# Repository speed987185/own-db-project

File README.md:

# Pi Cloud Server

A personal local cloud storage system built with Raspberry Pi.

---

## ⚠️ Prototype Notice

> **This repository contains a prototype implementation built for demonstration and submission purposes. The current version is developed and tested on a standard computer. Final deployment and hardware integration with Raspberry Pi will be performed after receiving approval from Blueprint Hack Club.**

---

## Project Overview

This project demonstrates a self-hosted cloud storage concept using:

- **Flask** backend with REST API
- **PostgreSQL** database for file metadata
- **Raspberry Pi** as target deployment platform

The goal is to create a personal alternative to commercial cloud storage services.

---

## Repository Contents

| Folder                                 | Description                         |
| -------------------------------------- | ----------------------------------- |
| `pi-cloud-server/`                     | Backend server (Flask + PostgreSQL) |
| `CAD/`                                 | 3D enclosure designs                |
| `PCB & SHEMANTIC FOR EXTERNALL BOARD/` | Custom PCB for Pi expansion         |

---

## Hardware Design

### PCB Design

Custom expansion board providing additional ports and cooling support.

### CAD Enclosure

3D-printable enclosure with:

- Front/back removable panels
- SSD mounting slot
- Port cutouts for Pi and expansion board

---

## Quick Start

```bash
cd pi-cloud-server
pip install -r requirements.txt
python app.py
```

See `pi-cloud-server/README.md` for detailed instructions.

---

## Future Plans (Post-Grant Approval)

- Raspberry Pi 4 deployment
- External SSD integration
- Full file upload/download
- Web dashboard
- User authentication

---

## Contact

Email: mjlabishek123@gmail.com

---

## License

MIT License

---

_Built for Blueprint Hack Club_

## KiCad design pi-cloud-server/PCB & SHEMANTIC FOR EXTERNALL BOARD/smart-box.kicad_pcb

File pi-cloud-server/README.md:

# Pi Cloud Server

A lightweight local cloud storage server designed for Raspberry Pi.

---

## ⚠️ Prototype Notice

> **This repository contains a prototype implementation built for demonstration and submission purposes. The current version is developed and tested on a standard computer. Final deployment and hardware integration with Raspberry Pi will be performed after receiving approval from Blueprint Hack Club.**

---

## What is this?

Pi Cloud Server is a self-hosted cloud storage solution that runs on a Raspberry Pi. It provides:

- **File metadata storage** using PostgreSQL database
- **REST API** for managing files
- **Local network access** to your personal cloud

Think of it as your own mini Dropbox, running on a $35 computer in your home.

---

## What this demonstrates

- Flask backend development
- SQLAlchemy ORM integration
- PostgreSQL database usage
- RESTful API design
- Modular Python project structure

---

## Project Structure

```
pi-cloud-server/
├── app.py           # Main Flask application
├── config.py        # Configuration settings
├── models.py        # Database models (SQLAlchemy)
├── routes.py        # API endpoints
├── requirements.txt # Python dependencies
├── schema.sql       # Database schema (optional)
├── TODO.md          # Future development plans
└── storage/         # File storage directory (future use)
```

---

## Quick Start

### 1. Install dependencies

```bash
pip install -r requirements.txt
```

### 2. Set up PostgreSQL database

```bash
# Create database
psql -U postgres -c "CREATE DATABASE picloud_db;"
psql -U postgres -c "CREATE USER picloud WITH PASSWORD 'password';"
psql -U postgres -c "GRANT ALL PRIVILEGES ON DATABASE picloud_db TO picloud;"
```

### 3. Run the server

```bash
python app.py
```

Server will start at `http://localhost:5000`

---

## API Endpoints

| Method | Endpoint | Description |
|--------|----------|-------------|
| GET | `/` | Server status |
| GET | `/files` | List all files |
| POST | `/files` | Create file metadata |
| GET | `/files/<id>` | Get single file |
| DELETE | `/files/<id>` | Delete file |
| GET | `/stats` | Storage statistics |

---

## Example Usage

### Check server status
```bash
curl http://localhost:5000/
```

### Create file metadata
```bash
curl -X POST http://localhost:5000/files \
  -H "Content-Type: application/json" \
  -d '{"filename": "document.pdf", "size": 1024, "file_type": "application/pdf"}'
```

### List all files
```bash
curl http://localhost:5000/files
```

### Delete a file
```bash
curl -X DELETE http://localhost:5000/files/1
```

---

## Database Configuration

Default connection string:
```
postgresql://picloud:password@localhost:5432/picloud_db
```

Override with environment variable:
```bash
export DATABASE_URL="postgresql://user:pass@host:port/dbname"
```

---

## Future Plans

After Blueprint Hack Club grant approval:

- Deploy on Raspberry Pi 4
- Integrate external SSD storage
- Add actual file upload/download
- Implement user authentication
- Create web dashboard

See `TODO.md` for full roadmap.

---

## Tech Stack

- **Backend:** Python, Flask
- **Database:** PostgreSQL, SQLAlchemy
- **Target Hardware:** Raspberry Pi 4

---

## License

MIT License

---

*Built for Blueprint Hack Club*

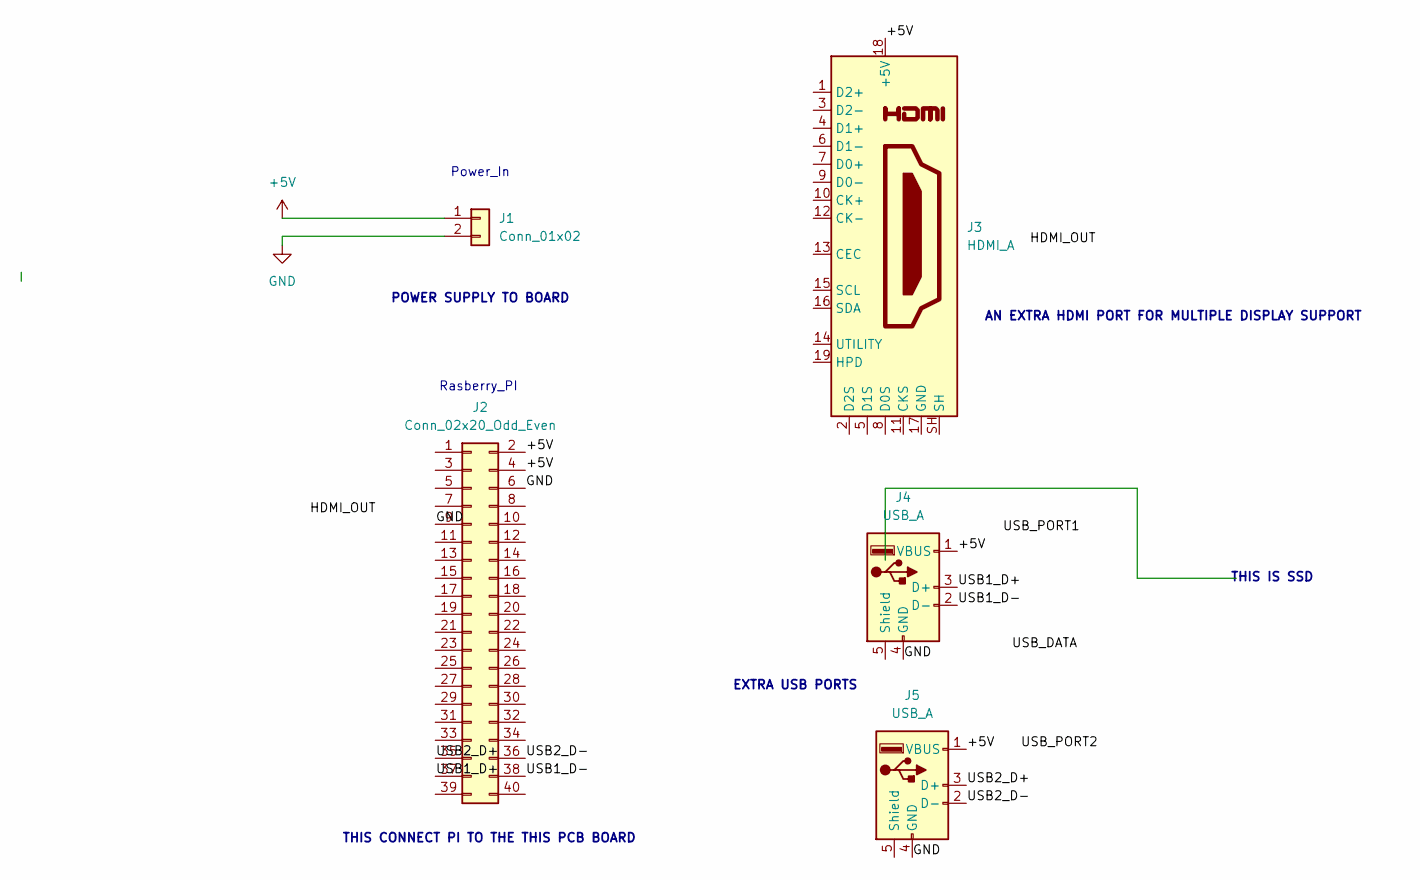
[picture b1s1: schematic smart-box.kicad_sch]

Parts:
J1: Conn_01x02; TerminalBlock_Xinya_XY308-2.54-2P_1x02_P2.54mm_Horizontal
J2: Conn_02x20_Odd_Even; PinHeader_2x20_P2.54mm_Vertical
J3: HDMI_A; HDMI_A_Molex_208658-1001_Horizontal
J4, J5: USB_A; USB_A_Molex_48037-2200_Horizontal

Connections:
+5V: J1.1, J2.2, J2.4, J3.18 (+5V), J4.1 (VBUS), J5.1 (VBUS)
/USB1_D+: J2.37, J4.3 (D+)
/USB1_D-: J2.38, J4.2 (D-)
/USB2_D+: J2.35, J5.3 (D+)
/USB2_D-: J2.36, J5.2 (D-)
GND: J1.2, J2.6, J2.9, J4.4 (GND), J5.4 (GND)

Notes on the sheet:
EXTRA USB PORTS
AN EXTRA HDMI PORT FOR MULTIPLE DISPLAY SUPPORT
THIS IS SSD
POWER SUPPLY TO BOARD
Power_In
THIS CONNECT PI TO THE THIS PCB BOARD
Rasberry_PI

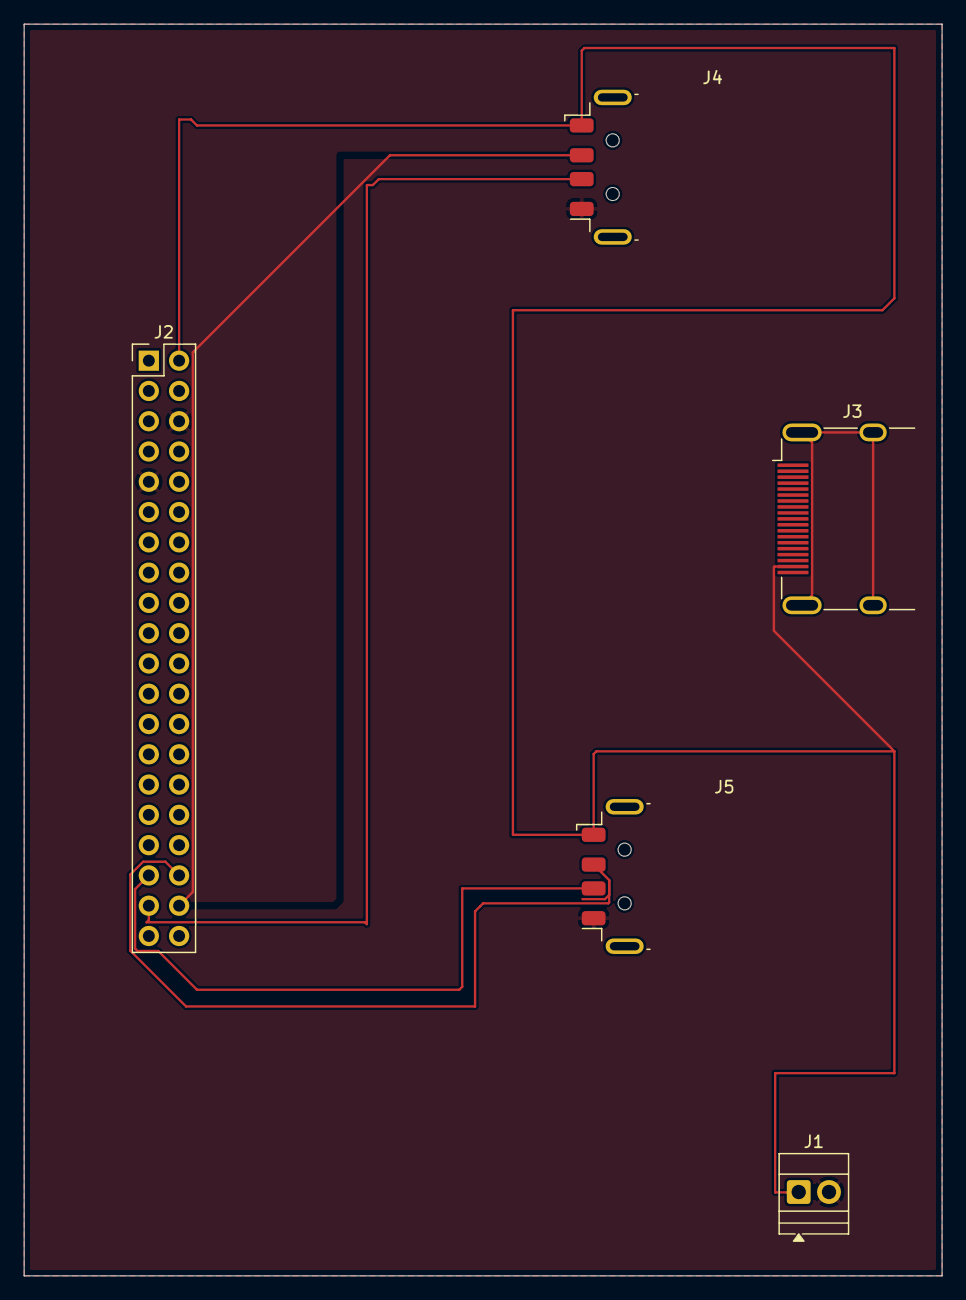
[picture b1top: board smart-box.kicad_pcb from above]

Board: 2 copper layers, 77.0 x 105.0 mm, 5 parts (0 on the bottom side), 6 nets.

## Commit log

2026-03-31 Revise TODO.md with project details and features
    Updated the project roadmap with a description, features, and notes.
2026-03-31 Revise README content and structure
    Updated README with new project description, features, and sections.
2026-03-31 Document external PCB board in README
    Added note about external PCB board for additional connections.
2026-03-31 Rename smart-box.kicad_pcb to pi-cloud-server/PCB & SHEMANTIC FOR EXTERNALL BOARD/smart-box.kicad_pcb
2026-03-31 Rename smart-box.kicad_sch to pi-cloud-server/PCB & SHEMANTIC FOR EXTERNAL BOARDsmart-box.kicad_sch
2026-03-31 Rename PCB & SHEMANTIC FOR EXTERNAL BOARDsmart-box.kicad_sch to PCB & SHEMANTIC FOR EXTERNALL BOARDsmart-box.kicad_sch
2026-03-31 Rename pi-cloud-server/PCB & SHEMANTIC FOR EXTERNALL BOARDsmart-box.kicad_sch to pi-cloud-server/PCB & SHEMANTIC FOR EXTERNALL BOARD/smart-box.kicad_sch
2026-03-31 Rename pi-cloud-server/PCB & SHEMANTIC FOR EXTERNALL BOARD/smart-box.kicad_pcb to PCB & SHEMANTIC FOR EXTERNALL BOARD/smart-box.kicad_pcb
2026-03-31 Rename pi-cloud-server/PCB & SHEMANTIC FOR EXTERNALL BOARD/smart-box.kicad_sch to PCB & SHEMANTIC FOR EXTERNALL BOARD/smart-box.kicad_sch
2026-03-31 Rename pi-cloud-server/README.md to README.md
2026-03-31 Rename database_back.step to CAD/database_back.step
2026-03-31 Rename database_front.step to CAD/database_front.step
2026-03-31 Rename Database_fullbody.step to CAD/Database_fullbody.step
2026-03-31 Big Update
